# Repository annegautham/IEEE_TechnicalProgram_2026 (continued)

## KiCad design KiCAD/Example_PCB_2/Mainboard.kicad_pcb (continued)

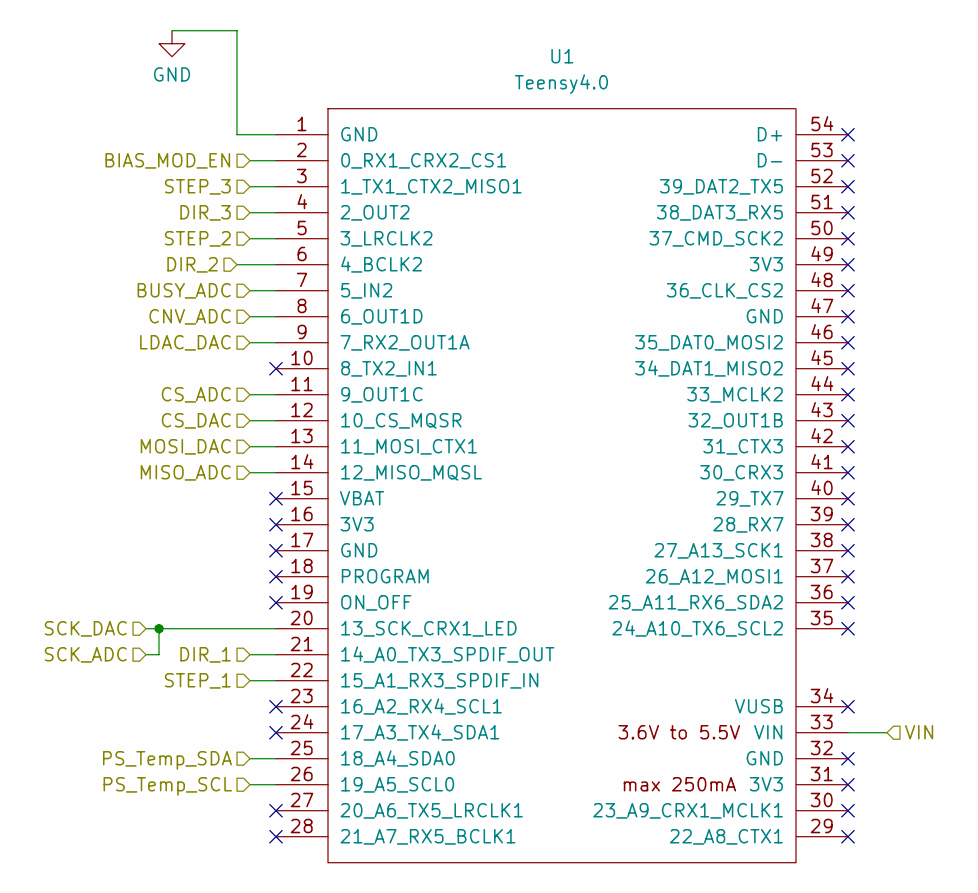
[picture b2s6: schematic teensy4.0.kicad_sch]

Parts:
U1: Teensy4.0; Teensy40

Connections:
+5V: U1.33 (VIN); also elsewhere on the board
/BIAS_MOD_EN: U1.2 (0_RX1_CRX2_CS1); also elsewhere on the board
/BUSY_ADC: U1.7 (5_IN2); also elsewhere on the board
/CNV_ADC: U1.8 (6_OUT1D); also elsewhere on the board
/CS_ADC: U1.11 (9_OUT1C); also elsewhere on the board
/CS_DAC: U1.12 (10_CS_MQSR); also elsewhere on the board
/LDAC_DAC: U1.9 (7_RX2_OUT1A); also elsewhere on the board
/MISO_ADC: U1.14 (12_MISO_MQSL); also elsewhere on the board
/MOSI_DAC: U1.13 (11_MOSI_CTX1); also elsewhere on the board
/PS_Temp_SCL: U1.26 (19_A5_SCL0); also elsewhere on the board
/PS_Temp_SDA: U1.25 (18_A4_SDA0); also elsewhere on the board
/SCK_ADC: U1.20 (13_SCK_CRX1_LED); also elsewhere on the board
/StepperDrivers/DIR_1: U1.21 (14_A0_TX3_SPDIF_OUT); also elsewhere on the board
/StepperDrivers/DIR_2: U1.6 (4_BCLK2); also elsewhere on the board
/StepperDrivers/DIR_3: U1.4 (2_OUT2); also elsewhere on the board
/StepperDrivers/STEP_1: U1.22 (15_A1_RX3_SPDIF_IN); also elsewhere on the board
/StepperDrivers/STEP_2: U1.5 (3_LRCLK2); also elsewhere on the board
/StepperDrivers/STEP_3: U1.3 (1_TX1_CTX2_MISO1); also elsewhere on the board
GND: U1.1 (GND); also elsewhere on the board

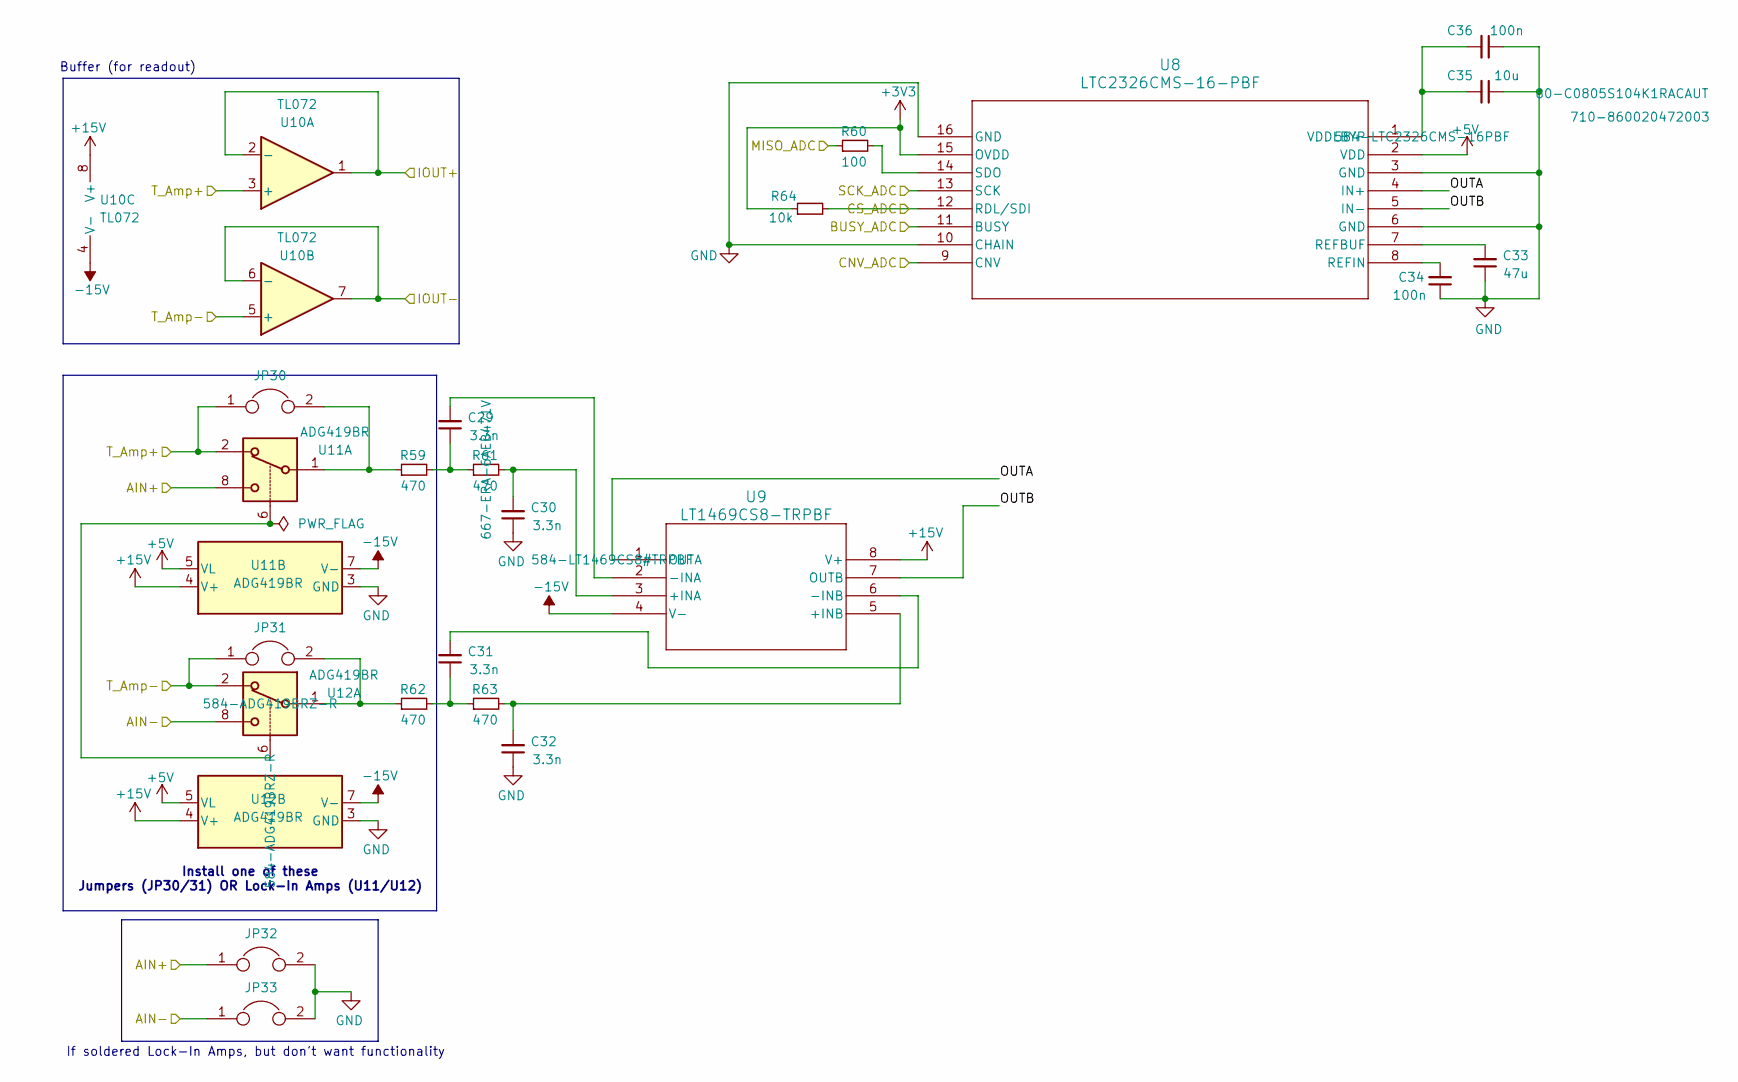
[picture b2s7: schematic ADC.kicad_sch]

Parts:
C29, C30, C31, C32: 3.3n; C_0805_2012Metric; Mouser Part Number 80-C0805C332KCR
C33: 47u; C_0805_2012Metric; Mouser Part Number 80-C0805C476M9P7800
C34, C36: 100n; C_0805_2012Metric; Mouser Part Number 80-C0805S104K1RACAUT
C35: 10u; CP_Radial_D5.0mm_P2.00mm; Mouser Part Number 710-860020472003
JP30, JP31, JP32, JP33: Jumper; SolderJumper-2_P1.3mm_Open_TrianglePad1.0x1.5mm
R59, R61, R62, R63: 470; R_0805_2012Metric; Mouser Part Number 667-ERA-6AEB471V
R60: 100; R_0805_2012Metric; Mouser Part Number 708-RNCA0805BTE100R
R64: 10k; R_0805_2012Metric; Mouser Part Number 755-ESR10EZPD1002
U8: LTC2326CMS-16-PBF; MSOP-16_MS_LIT; Mouser Part Number 584-LTC2326CMS-16PBF
U9: LT1469CS8-TRPBF; SO-8_S_LIT; Mouser Part Number 584-LT1469CS8#TRPBF
U10: TL072; SOIC-8-1EP_3.9x4.9mm_P1.27mm_EP2.29x3mm_ThermalVias; Mouser Part Number 511-TL072BIDT
U11, U12: ADG419BR; SOIC-8_3.9x4.9mm_P1.27mm; Mouser Part Number 584-ADG419BRZ-R

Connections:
+3V3: R64.1, U8.15 (OVDD); also elsewhere on the board
+5V: U8.2 (VDD), U11.5 (VL), U12.5 (VL); also elsewhere on the board
+15V: U9.8 (V+), U10.8 (V+), U11.4 (V+), U12.4 (V+); also elsewhere on the board
-15V: U9.4 (V-), U10.4 (V-), U11.7 (V-), U12.7 (V-); also elsewhere on the board
/ADC/OUTA: U8.4 (IN+), U9.1 (OUTA)
/ADC/OUTB: U8.5 (IN-), U9.7 (OUTB)
/AIN+: JP32.1, U11.8; also elsewhere on the board
/AIN-: JP33.1, U12.8; also elsewhere on the board
/BUSY_ADC: U8.11 (BUSY); also elsewhere on the board
/CNV_ADC: U8.9 (CNV); also elsewhere on the board
/CS_ADC: R64.2, U8.12 (RDL/SDI); also elsewhere on the board
/IOUT+: U10.1, U10.2 (-); also elsewhere on the board
/IOUT-: U10.6 (-), U10.7; also elsewhere on the board
/MISO_ADC: R60.1; also elsewhere on the board
/SCK_ADC: U8.13 (SCK); also elsewhere on the board
/T_Amp+: JP30.1, U10.3 (+), U11.2; also elsewhere on the board
/T_Amp-: JP31.1, U10.5 (+), U12.2; also elsewhere on the board
GND: C30.1, C32.1, C33.1, C34.1, C35.1, C36.1, JP32.2, JP33.2, U8.3 (GND), U8.6 (GND), U8.10 (CHAIN), U8.16 (GND), U11.3 (GND), U12.3 (GND); also elsewhere on the board
unnamed: C29.1, R59.2, R61.1
unnamed: C31.1, R62.2, R63.1
unnamed: JP30.2, R59.1, U11.1
unnamed: JP31.2, R62.1, U12.1
unnamed: C33.2, U8.7 (REFBUF)
unnamed: C34.2, U8.8 (REFIN)
unnamed: R60.2, U8.14 (SDO)
unnamed: C35.2, C36.2, U8.1 (VDDLBYP)
unnamed: C30.2, R61.2, U9.3 (+INA)
unnamed: C32.2, R63.2, U9.5 (+INB)
unnamed: C29.2, U9.2 (-INA)
unnamed: C31.2, U9.6 (-INB)
unnamed: U11.6, U12.6

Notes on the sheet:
Install one of these Jumpers (JP30/31) OR Lock-In Amps (U11/U12)
If soldered Lock-In Amps, but don't want functionality
Buffer (for readout)

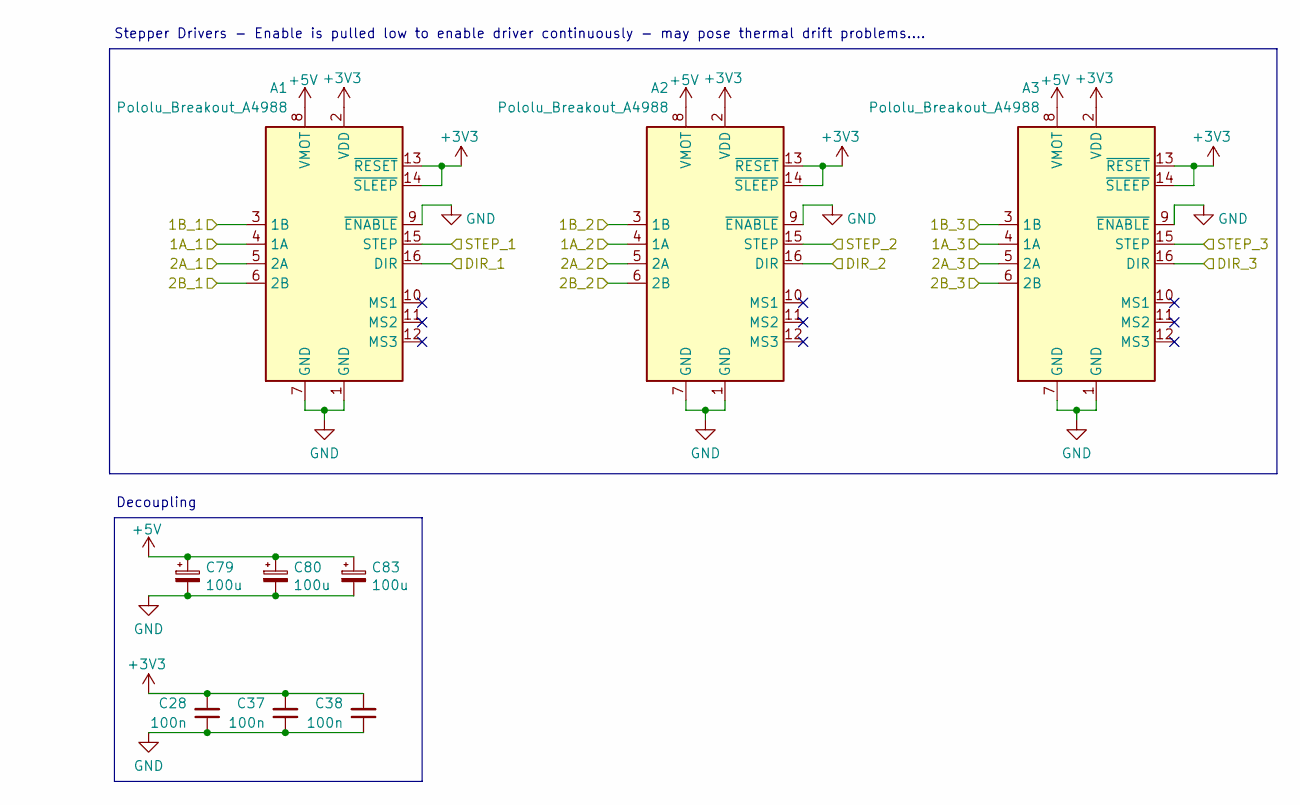
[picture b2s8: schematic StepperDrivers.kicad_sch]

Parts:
A1, A2, A3: Pololu_Breakout_A4988; Pololu_Breakout-16_15.2x20.3mm
C28, C37, C38: 100n; C_0805_2012Metric; Mouser Part Number 80-C0805S104K1RACAUT
C79, C80, C83: 100u; CP_Radial_D6.3mm_P2.50mm; Mouser Part Number 80-ESW107M016AE3EA

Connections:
+3V3: A1.2 (VDD), A1.13 (~RESET), A1.14 (~SLEEP), A2.2 (VDD), A2.13 (~RESET), A2.14 (~SLEEP), A3.2 (VDD), A3.13 (~RESET), A3.14 (~SLEEP), C28.2, C37.2, C38.2; also elsewhere on the board
+5V: A1.8 (VMOT), A2.8 (VMOT), A3.8 (VMOT), C79.1, C80.1, C83.1; also elsewhere on the board
/1A_1: A1.4 (1A); also elsewhere on the board
/1A_2: A2.4 (1A); also elsewhere on the board
/1A_3: A3.4 (1A); also elsewhere on the board
/1B_1: A1.3 (1B); also elsewhere on the board
/1B_2: A2.3 (1B); also elsewhere on the board
/1B_3: A3.3 (1B); also elsewhere on the board
/2A_1: A1.5 (2A); also elsewhere on the board
/2A_2: A2.5 (2A); also elsewhere on the board
/2A_3: A3.5 (2A); also elsewhere on the board
/2B_1: A1.6 (2B); also elsewhere on the board
/2B_2: A2.6 (2B); also elsewhere on the board
/2B_3: A3.6 (2B); also elsewhere on the board
/StepperDrivers/DIR_1: A1.16 (DIR); also elsewhere on the board
/StepperDrivers/DIR_2: A2.16 (DIR); also elsewhere on the board
/StepperDrivers/DIR_3: A3.16 (DIR); also elsewhere on the board
/StepperDrivers/STEP_1: A1.15 (STEP); also elsewhere on the board
/StepperDrivers/STEP_2: A2.15 (STEP); also elsewhere on the board
/StepperDrivers/STEP_3: A3.15 (STEP); also elsewhere on the board
GND: A1.1 (GND), A1.7 (GND), A1.9 (~ENABLE), A2.1 (GND), A2.7 (GND), A2.9 (~ENABLE), A3.1 (GND), A3.7 (GND), A3.9 (~ENABLE), C28.1, C37.1, C38.1, C79.2, C80.2, C83.2; also elsewhere on the board

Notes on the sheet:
Stepper Drivers - Enable is pulled low to enable driver continuously - may pose thermal drift problems....
Decoupling

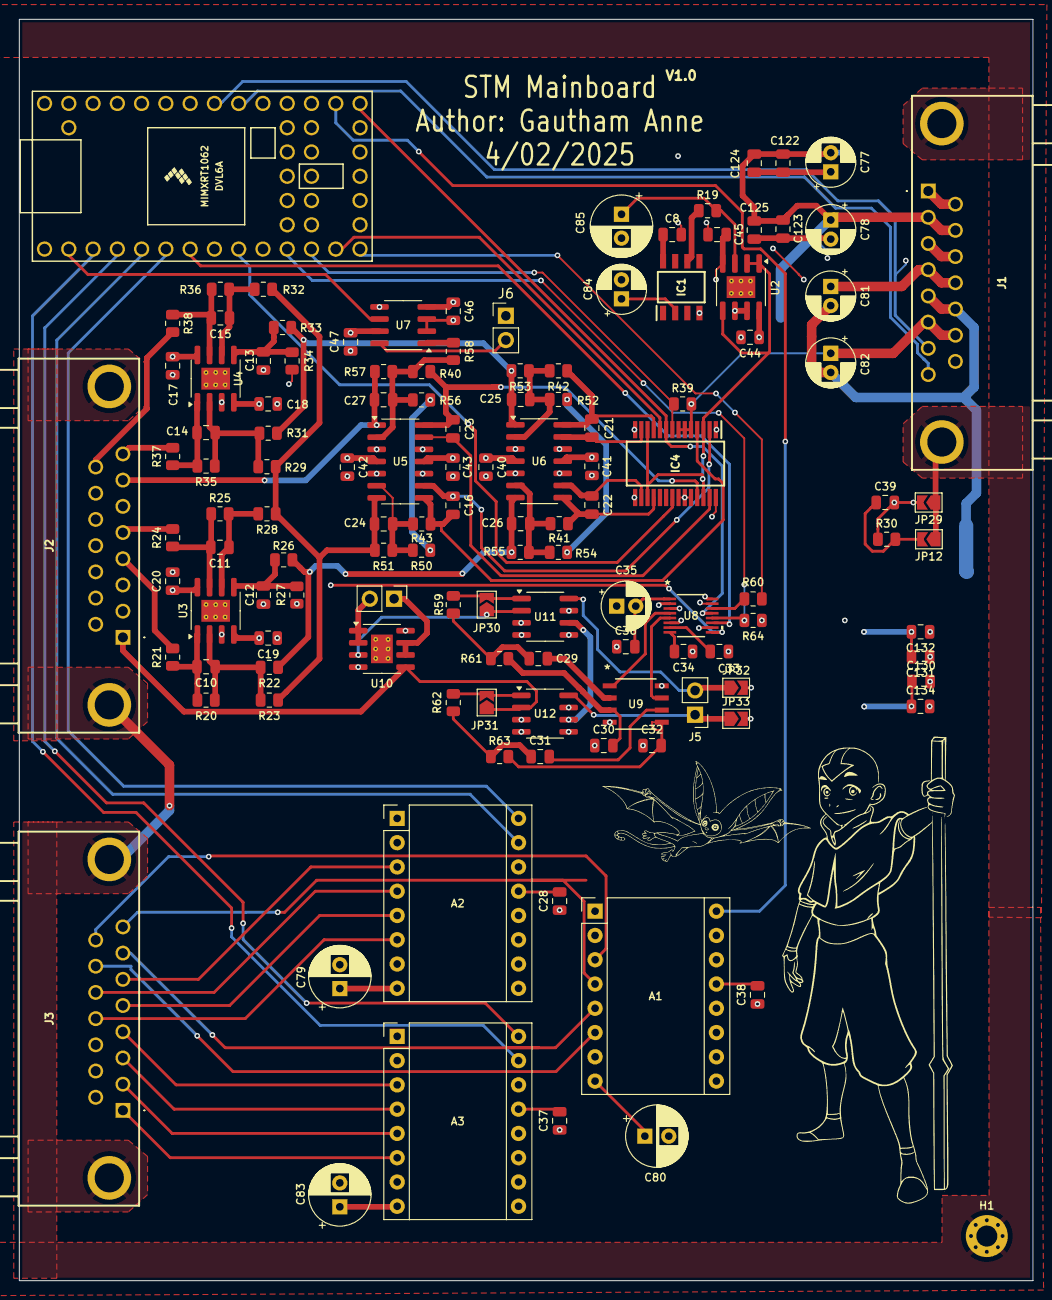
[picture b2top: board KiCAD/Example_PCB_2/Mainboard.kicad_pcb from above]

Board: 4 copper layers, 106.1 x 132.0 mm, 126 parts (0 on the bottom side), 94 nets.

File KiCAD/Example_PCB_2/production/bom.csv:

Designator,Footprint,Quantity,Value,LCSC Part #
"A1, A2, A3",Pololu_Breakout-16_15.2x20.3mm,3,Pololu_Breakout_A4988,
"C10, C11, C12, C13, C14, C15, C24, C25, C26, C27",0805,10,4.7n,
"C122, C123, C124, C125, C130, C131, C132, C134",0805,8,100n,
"C16, C21, C22, C23, C29, C30, C31, C32",0805,8,3.3n,
"C17, C18, C19, C20, C39, C40, C41, C42, C43, C44, C45, C46, C47",0805,13,100n,C14663
"C28, C34, C36, C37, C38",0805,5,100n,
C33,0805,1,47u,
"C35, C77, C78, C81, C82, C84",CP_Radial_D5.0mm_P2.00mm,6,10u,
"C79, C80, C83, C85",CP_Radial_D6.3mm_P2.50mm,4,100u,
C8,0805,1,2.2u,
IC1,SOIC127P600X175-8N,1,REF102AU_2K5,
IC4,SOP65P780X200-28N,1,DAC8814IBDBT,
"J1, J2, J3",57457826,3,5745782-6,
"J4, J5, J6",PinHeader_1x02_P2.54mm_Vertical,3,Conn_01x02_Pin,
"JP12, JP29, JP30, JP31, JP32, JP33",SolderJumper-2_P1.3mm_Open_TrianglePad1.0x1.5mm,6,Jumper,
R19,0805,1,1k,
"R20, R22, R23, R25, R26, R27, R28, R29, R31, R32, R33, R34, R35, R36, R50, R51, R52, R53, R54, R55, R56, R57, R58",0805,23,3k,
"R21, R24, R37, R38",0805,4,220,
R30,0805,1,1M2,C22107
"R39, R64",0805,2,10k,
"R40, R41, R42, R43",0805,4,1.5k,
"R59, R61, R62, R63",0805,4,470,
R60,0805,1,100,
U1,Teensy40,1,Teensy4.0,
"U10, U2, U3, U4",SOIC-8-1EP_3.9x4.9mm_P1.27mm_EP2.29x3mm_ThermalVias,4,TL072,
"U11, U12, U7",SOIC-8_3.9x4.9mm_P1.27mm,3,ADG419BR,
"U5, U6",SOIC-14_3.9x8.7mm_P1.27mm,2,TL074,
U8,MSOP-16_MS_LIT,1,LTC2326CMS-16-PBF,
U9,SO-8_S_LIT,1,LT1469CS8-TRPBF,

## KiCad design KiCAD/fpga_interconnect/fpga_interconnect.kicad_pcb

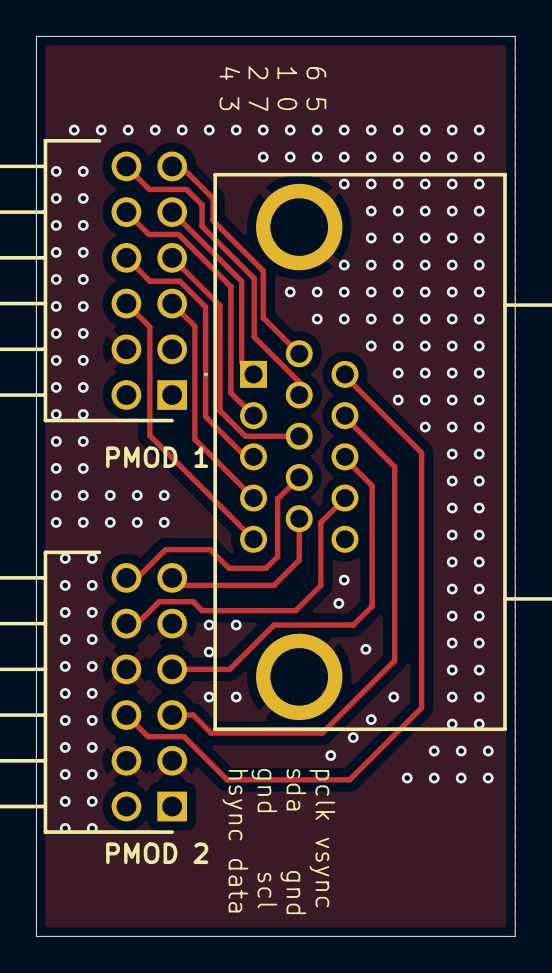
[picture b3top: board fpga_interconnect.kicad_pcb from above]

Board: 2 copper layers, 26.6 x 50.0 mm, 3 parts (0 on the bottom side), 15 nets.

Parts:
J1: VGA; AHDF15AKGTAXB
J2: Pmod 1; HDRRA12W63P254_2X6_1514X280X635P
J3: Pmod 2; HDRRA12W63P254_2X6_1514X280X635P

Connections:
/DATAEN_CMD: J1.12, J3.5
/HSYNC: J1.11, J3.6
/IIC1_SCL: J1.13, J3.7
/IIC1_SDA: J1.14, J3.10
/PCLK: J1.9, J3.12
/PDATA0: J1.1, J2.9
/PDATA1: J1.2, J2.10
/PDATA2: J1.3, J2.8
/PDATA3: J1.4, J2.5
/PDATA4: J1.5, J2.6
/PDATA5: J1.6, J2.11
/PDATA6: J1.7, J2.12
/PDATA7: J1.8, J2.7
/VSYNC: J1.10, J3.11
GND: J1.15, J1.MH1, J1.MH2, J2.3, J2.4, J3.3, J3.4, J3.8, J3.9

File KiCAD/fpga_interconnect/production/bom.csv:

Designator,Footprint,Quantity,Value,LCSC Part #
J1,AHDF15AKGTAXB,1,VGA,
J2,HDRRA12W63P254_2X6_1514X280X635P,1,Pmod 1,
J3,HDRRA12W63P254_2X6_1514X280X635P,1,Pmod 2,

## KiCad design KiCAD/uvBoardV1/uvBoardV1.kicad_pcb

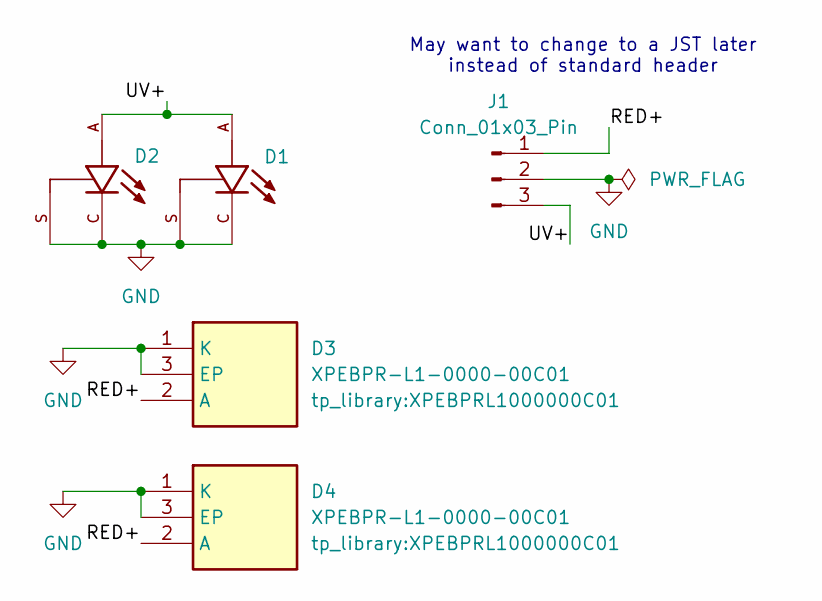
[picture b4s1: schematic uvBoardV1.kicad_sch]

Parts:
D1, D2: SST-10-UV-A130-G405-00; LED_SST-10-UV-A130-G405-00; PARTREV 05
D3, D4: XPEBPR-L1-0000-00C01; XPEBPRL1000000C01; Mouser Part Number 941-XPEBPRL10000C01
J1: Conn_01x03_Pin; PinHeader_1x03_P2.54mm_Vertical

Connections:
/RED+: D3.2 (A), D4.2 (A), J1.1
/UV+: D1.A, D2.A, J1.3
GND: D1.C, D1.S, D2.C, D2.S, D3.1 (K), D3.3 (EP), D4.1 (K), D4.3 (EP), J1.2

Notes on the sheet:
May want to change to a JST later instead of standard header

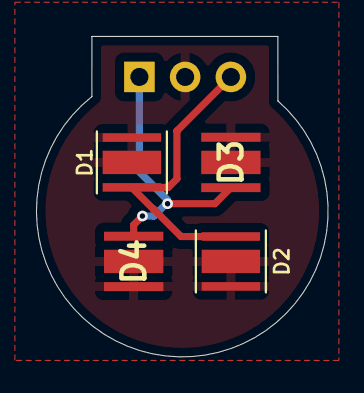
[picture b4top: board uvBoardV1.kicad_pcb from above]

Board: 2 copper layers, 16.2 x 17.8 mm, 5 parts (1 on the bottom side), 3 nets.

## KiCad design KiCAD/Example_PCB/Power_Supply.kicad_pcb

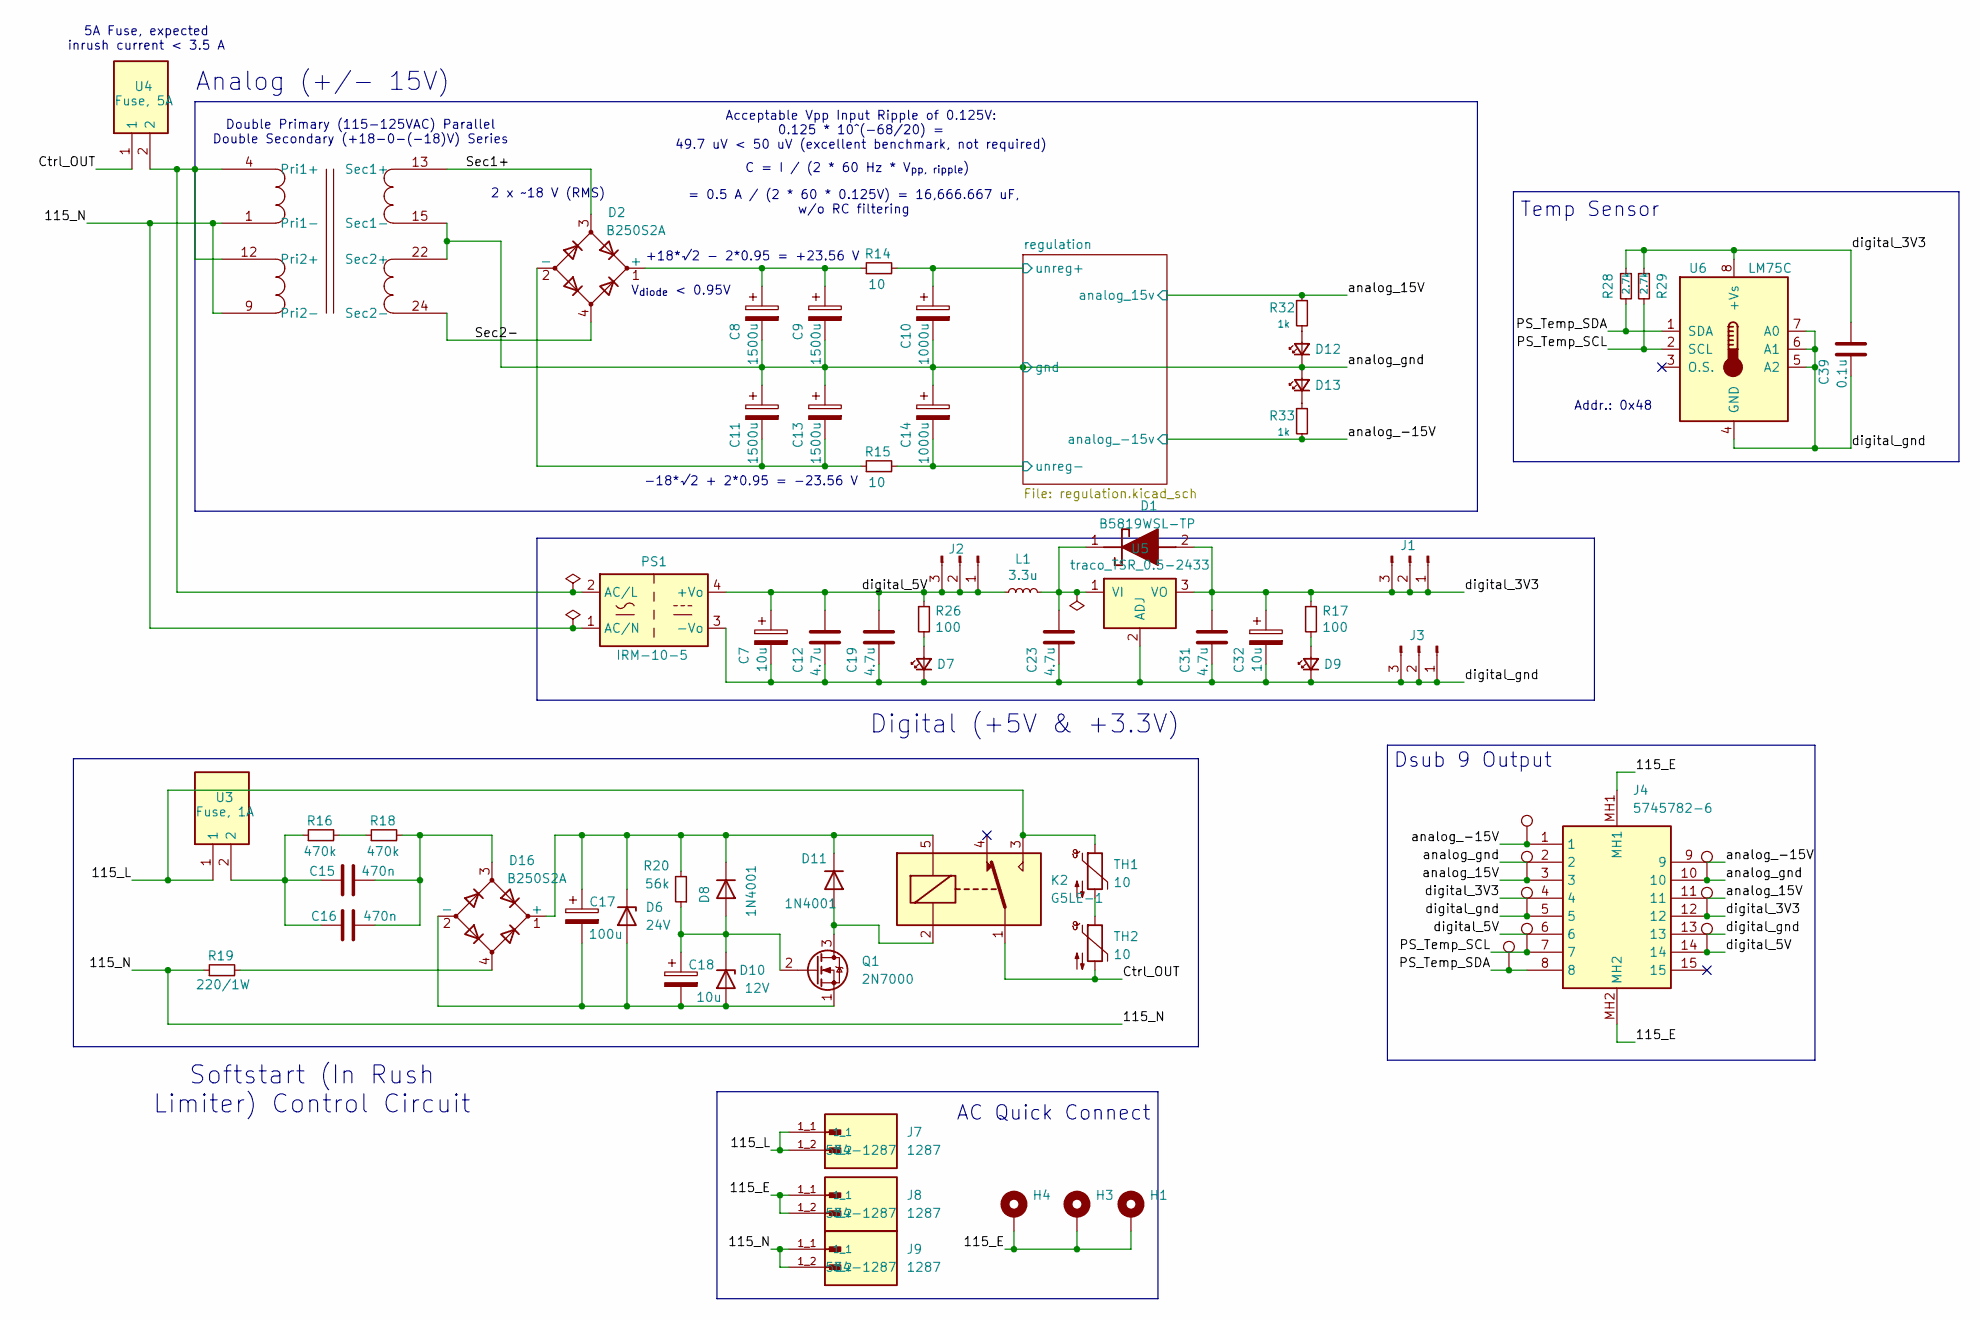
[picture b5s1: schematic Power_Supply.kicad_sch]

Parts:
C7, C32: 10u; CP_EIA-7343-31_Kemet-D; Mouser Part Number 80-T491D106K025
C8, C9, C11, C13: 1500u; CP_Radial_D12.5mm_P5.00mm_+Better; Mouser Part Number 647-UHW1H152MHD
C10, C14: 1000u; CP_Radial_D12.5mm_P5.00mm_+Better; Mouser Part Number 647-UHW1H102MHD
C12, C19, C23, C31: 4.7u; C_0603_1608Metric; Mouser Part Number 187-CL10A475KO8NQNC
C15, C16: 470n; CAP_R46KN347000N0M_KEM; Mouser Part Number 80-R46KN347000N0M
C17: 100u; C_Radial_D10.0mm_H12.5mm_P5.00mm; Mouser Part Number 594-2222-140-50101
C18: 10u; CP_Radial_D5.0mm_P2.00mm; Mouser Part Number 710-860010372001
C39: 0.1u; C_0603_1608Metric; Mouser Part Number 80-C0603C104J1RAUTO7
D1: B5819WSL-TP; SODFL2512X90N; Mouser Part Number 833-B5819WSL-TP
D2, D16: B250S2A; P20_SO-DIL-Slim; Mouser Part Number 637-B250S2A-SLIM
D6: 24V; D_SOD-123; Mouser Part Number 863-SZMMSZ4709T1G
D7, D9, D12, D13: LED_Small; LED_0603_1608Metric
D8, D11: 1N4001; D_DO-41_SOD81_P10.16mm_Horizontal; Mouser Part Number 637-1N4001
D10: 12V; D_SOD-123; Mouser Part Number 78-MMSZ4699-HE3_A-08
H1, H3, H4: MountingHole_Pad; MountingHole_3.2mm_M3_Pad_Via
J1, J2, J3: Conn_01x03_Pin; PinHeader_1x03_P2.54mm_Vertical
J4: 5745782-6; 57457826; Mouser Part Number 571-5745782-6
J7, J8, J9: 1287; KEYSTONE_1287; PARTREV F; Mouser Part Number 534-1287
K2: G5LE-1; Relay_SPDT_Omron-G5LE-1; Mouser Part Number 653-G5LE-1-SDC24
L1: 3.3u; IND_BOURNS_SRR1280; Mouser Part Number 652-SRR1280-3R3Y
PS1: IRM-10-5; Converter_ACDC_MeanWell_IRM-10-xx_THT; Mouser Part Number 709-IRM10-5
Q1: 2N7000; TO-92_Inline; Mouser Part Number 512-2N7000
R14, R15: 10; R_1206_3216Metric; Mouser Part Number 71-RCC120610R0JNEA
R16, R18: 470k; R_Axial_DIN0207_L6.3mm_D2.5mm_P15.24mm_Horizontal; Mouser Part Number 71-CCF07470KJKE36
R17, R26: 100; R_0805_2012Metric; Mouser Part Number 710-560112120020
R19: 220/1W; R_2512_6332Metric; Mouser Part Number 279-3520220RJT
R20: 56k; R_0805_2012Metric; Mouser Part Number 755-ESR10EZPF5602
R28, R29: 2.7k; R_0805_2012Metric; Mouser Part Number 603-AA0805JR-072K7L
R32, R33: 1k; R_0805_2012Metric
T1: FLN_40_18
TH1, TH2: 10; R_Axial_DIN0204_L3.6mm_D1.6mm_P5.08mm_Horizontal; Mouser Part Number 995-SL10-10002
TP1, TP2, TP3, TP4, TP5, TP6, TP7, TP8: TestPoint; TestPoint_Loop_D1.80mm_Drill1.0mm_Beaded; Mouser Part Number 534-5005
U3: Fuse, 1A; 0PTF0078P; Mouser Part Number 576-0PTF0078P
U4: Fuse, 5A; 0PTF0078P; Mouser Part Number 576-0PTF0078P
U5: traco_TSR_0.5-2433; TSR-0.5-2433; Mouser Part Number 495-TSR0.5-2433
U6: LM75C; SOIC-8_3.9x4.9mm_P1.27mm; Mouser Part Number 700-LM75BIM-3+

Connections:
/115_E: H1.1, H3.1, H4.1, J4.MH1, J4.MH2, J8.1_1, J8.1_2
/115_L: J7.1_1, J7.1_2, K2.3, TH1.1, U3.1
/115_N: J9.1_1, J9.1_2, PS1.1 (AC/N), R19.1, T1.1 (Pri1-), T1.9 (Pri2-)
/Ctrl_OUT: K2.1, TH2.2, U4.1
/PS_Temp_SCL: J4.7, R29.2, TP7.1, U6.2 (SCL)
/PS_Temp_SDA: J4.8, R28.2, TP8.1, U6.1 (SDA)
/Sec1+: D2.3, T1.13 (Sec1+)
/Sec2-: D2.4, T1.24 (Sec2-)
/analog_15V: J4.3, J4.11, R32.1, TP3.1; also elsewhere on the board
/analog_-15V: J4.1, J4.9, R33.2, TP1.1; also elsewhere on the board
/analog_gnd: C8.2, C9.2, C10.2, C11.1, C13.1, C14.1, D12.1 (K), D13.2 (A), J4.2, J4.10, T1.15 (Sec1-), T1.22 (Sec2+), TP2.1; also elsewhere on the board
/digital_3V3: C31.1, C32.1, C39.1, D1.2 (A), J1.1, J1.2, J1.3, J4.4, J4.12, R17.1, R28.1, R29.1, TP4.1, U5.3 (VO), U6.8 (+Vs)
/digital_5V: C7.1, C12.1, C19.1, J2.1, J2.2, J2.3, J4.6, J4.14, L1.1, PS1.4 (+Vo), R26.1, TP6.1
/digital_gnd: C7.2, C12.2, C19.2, C23.2, C31.2, C32.2, C39.2, D7.1 (K), D9.1 (K), J3.1, J3.2, J3.3, J4.5, J4.13, PS1.3 (-Vo), TP5.1, U5.2 (ADJ), U6.4 (GND), U6.5 (A2), U6.6 (A1), U6.7 (A0)
/regulation/unreg+: C10.1, R14.2; also elsewhere on the board
/regulation/unreg-: C14.2, R15.2; also elsewhere on the board
unnamed: C15.1, C16.1, R16.1, U3.2
unnamed: C15.2, C16.2, D16.3, R18.2
unnamed: C23.1, D1.1 (K), L1.2, U5.1 (VI)
unnamed: C8.1, C9.1, D2.1 (+), R14.1
unnamed: C11.2, C13.2, D2.2 (-), R15.1
unnamed: D7.2 (A), R26.2
unnamed: D9.2 (A), R17.2
unnamed: C17.2, C18.2, D6.2 (A), D10.2 (A), D16.2 (-), Q1.1 (S)
unnamed: C18.1, D8.2 (A), D10.1 (K), Q1.2 (G), R20.1
unnamed: D11.2 (A), K2.2, Q1.3 (D)
unnamed: C17.1, D6.1 (K), D8.1 (K), D11.1 (K), D16.1 (+), K2.5, R20.2
unnamed: D12.2 (A), R32.2
unnamed: D13.1 (K), R33.1
unnamed: D16.4, R19.2
unnamed: PS1.2 (AC/L), T1.4 (Pri1+), T1.12 (Pri2+), U4.2
unnamed: R16.2, R18.1
unnamed: TH1.2, TH2.1

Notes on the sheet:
Dsub 9 Output
Addr.: 0x48
Analog (+/- 15V)
5A Fuse, expected inrush current < 3.5 A
Acceptable Vpp Input Ripple of 0.125V: 0.125 * 10^(-68/20) = 49.7 uV < 50 uV (excellent benchmark, not required)
Double Primary (115-125VAC) Parallel Double Secondary (+18-0-(-18)V) Series
Softstart (In Rush Limiter) Control Circuit
-18*√2 + 2*0.95 = -23.56 V
C = I / (2 * 60 Hz * V_{pp, ripple})
V_{diode} < 0.95V
AC Quick Connect
2 x ~18 V (RMS)
Temp Sensor
+18*√2 - 2*0.95 = +23.56 V
Digital (+5V & +3.3V)
= 0.5 A / (2 * 60 * 0.125V) = 16,666.667 uF, w/o RC filtering

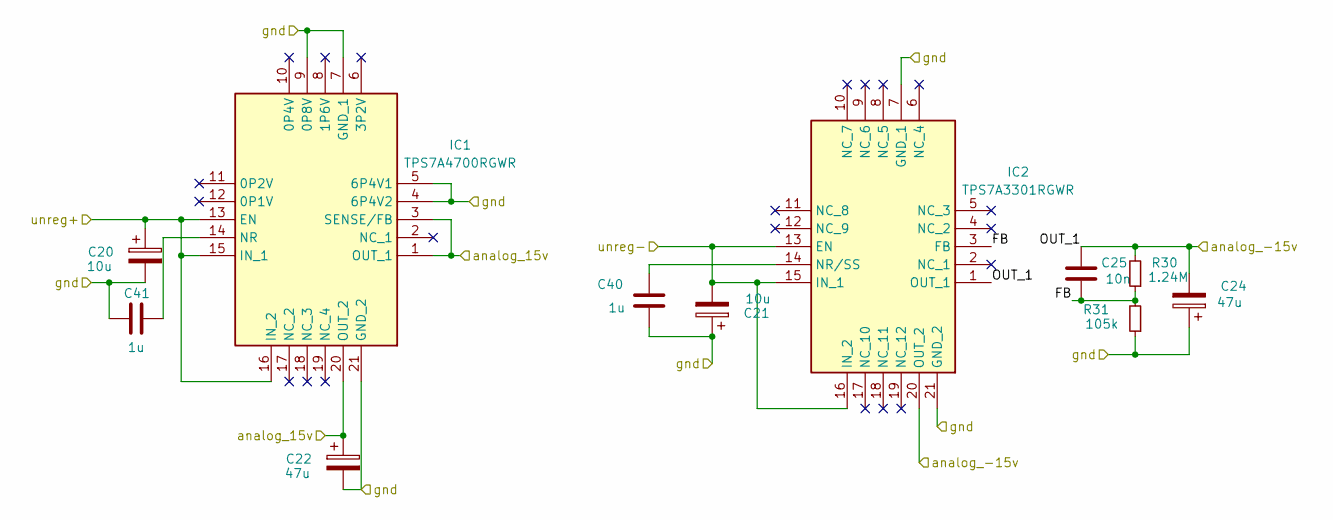
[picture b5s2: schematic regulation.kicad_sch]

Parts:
C20, C21: 10u; CP_EIA-7343-31_Kemet-D; Mouser Part Number 80-T491D106K025
C22, C24: 47u; CP_EIA-7343-31_Kemet-D; Mouser Part Number 80-T491D476K020
C25: 10n; C_0603_1608Metric; Mouser Part Number 581-06033C103KAZ2A
C40, C41: 1u; C_0603_1608Metric; Mouser Part Number 963-MLASU168SB5105KT
IC1: TPS7A4700RGWR; QFN65P500X500X100-21N-D; Mouser Part Number 595-TPS7A4700RGWR
IC2: TPS7A3301RGWR; QFN65P500X500X100-21N-D; Mouser Part Number 595-TPS7A3301RGWR
R30: 1.24M; R_0805_2012Metric; Mouser Part Number 71-CRCW08051M24FKEA
R31: 105k; R_0805_2012Metric; Mouser Part Number 279-RQ73C2A105KBTD

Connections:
/analog_15V: C22.1, IC1.1 (OUT_1), IC1.3 (SENSE/FB), IC1.20 (OUT_2); also elsewhere on the board
/analog_-15V: C24.2, C25.1, IC2.1 (OUT_1), IC2.20 (OUT_2), R30.2; also elsewhere on the board
/analog_gnd: C20.2, C21.1, C22.2, C24.1, C40.2, C41.2, IC1.4 (6P4V2), IC1.5 (6P4V1), IC1.7 (GND_1), IC1.9 (0P8V), IC1.21 (GND_2), IC2.7 (GND_1), IC2.21 (GND_2), R31.1; also elsewhere on the board
/regulation/FB: C25.2, IC2.3 (FB), R30.1, R31.2
/regulation/unreg+: C20.1, IC1.13 (EN), IC1.15 (IN_1), IC1.16 (IN_2); also elsewhere on the board
/regulation/unreg-: C21.2, IC2.13 (EN), IC2.15 (IN_1), IC2.16 (IN_2); also elsewhere on the board
unnamed: C41.1, IC1.14 (NR)
unnamed: C40.1, IC2.14 (NR/SS)

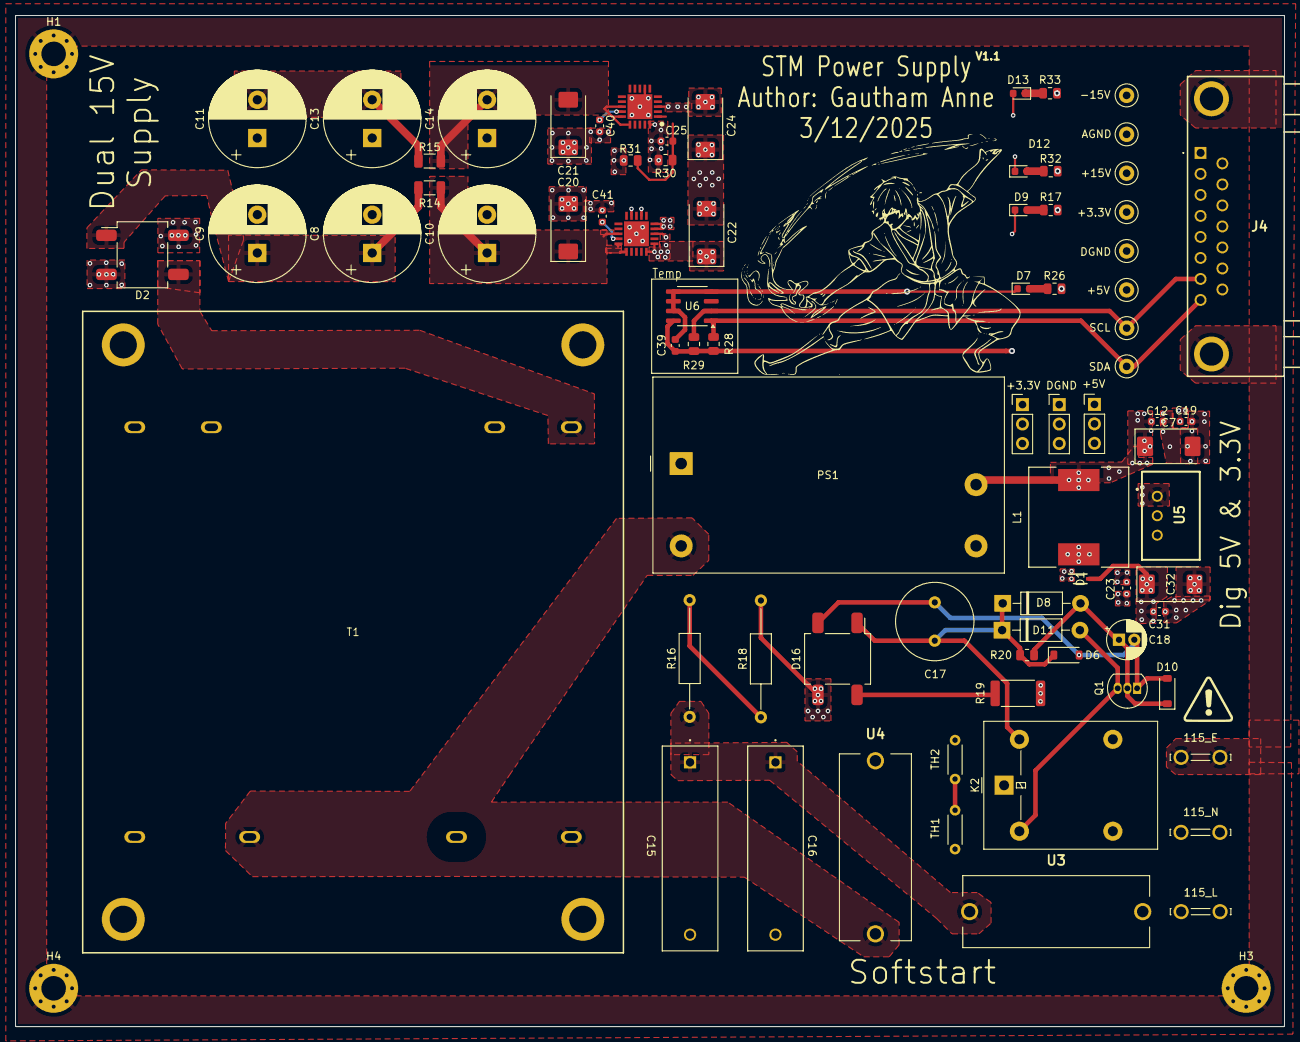
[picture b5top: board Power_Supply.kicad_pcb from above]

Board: 4 copper layers, 165.7 x 132.0 mm, 80 parts (0 on the bottom side), 36 nets.

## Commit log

2026-01-31 example pcb + diffraction eff calculator
2026-02-02 empty pcb and sch files
2026-02-02 added a non-functioning .py file that's supposed to generate the footprint, needs debugging and entering correct values cause this is ai's work
2026-02-06 library .pretty is created, with DLPC footprint python code successfully generting footprint, should double check if the specefications match datasheet exactly
2026-02-06 added four boards in a root screen sheet
2026-02-12 crime
2026-02-14 uv pcb
2026-02-14 bga footprint addition
2026-02-15 symbol add
2026-02-15 dlpa2005 symbol + footprint added to proj specific library
2026-02-15 some doofus goofus
2026-02-15 Val's edit
2026-02-15 val new edit brr
2026-02-16 changed tp_library to read & write
2026-02-16 stepper updates
2026-02-16 moved capacitor
2026-02-17 pain! dmd interface grind part 1
2026-02-17 spi connections to dlpc
2026-02-17 dmd interface done!
2026-02-18 humanly readable now
2026-02-18 more readable
2026-02-18 some new schematics
2026-02-18 some schematic layout power
2026-02-18 WIP dmd interface; made assembly for DMD, started new board for DMD interconnect
2026-02-18 assembly for lga footprint
2026-02-19 almost done with VSS, VDD without power souce schematics
2026-02-20 no major changes
2026-02-21 fixed some DRC error
2026-02-21 didn't really change mainboard
2026-02-23 non finished changes
2026-02-24 commiting progress hope this doesn't crash
2026-02-24 DLPC pins all connected to pin, some circutry incomplete inclding LEDs, SPI, Crystal Ocillator, and DLPC programming flash. I also need to import a symbol and footprint for the ferrite beads, and som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
2026-02-24 relative library paths
2026-02-25 firmware for stepper
2026-02-25 software gui update
2026-02-26 pully pull
2026-02-26 #stillonthegrind
2026-02-26 yaaaa
2026-02-26 minor changed
2026-02-27 Changed all FPGA Connections to what we want, created a new project for the connection board
2026-02-28 actually saved the file this time
2026-02-28 SPI and prog connection
2026-02-28 Added our connector board from FPGA to main board
2026-02-28 added 3d models to FPGA Board
2026-02-28 fixed bus connection on fpga connector
2026-03-01 fixed pdata bus connection
2026-03-01 fixed funny bus connectinos
2026-03-01 gpios are now hierarchicals
2026-03-01 fixed spi1 dlpc connections
2026-03-01 fixed all proj specific compoents
2026-03-01 name changes cuz i like lowercase
2026-03-01 fun changes
2026-03-01 uv board productino files
2026-03-01 dmd interconnect work 1st pass
2026-03-01 mainboard pain
2026-03-01 Complete FPGA interconnect
2026-03-01 DLPC schematic looks a bit prettier now, ERC needs to be resolved, the vast majority of errors are because global label is not connected to anything, a good amount of housekeeping left before I can s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
2026-03-03 productino files
2026-03-03 added interactive html bom for fpga interconnect
2026-03-04 first pass optics
2026-03-05 Backlink to CADLAB.io has been added.
2026-03-05 added footprints
2026-03-05 designator names fixed
2026-03-05 rawr
2026-03-06 Testing Motors code added
2026-03-07 fixed VSS, VDD, VCC labels to match their hierarchical counterparts
2026-03-07 added text labels with explainations, check out the updates spreadsheet too - still not complete
2026-03-08 designator names on global finally
2026-03-08 fixed more ERCs
2026-03-09 started power gen input schematic, need to source correct input for 5V buck converter, finished 5V to 3v3 buck converter, need to start the 1.2, 1.8, and buffer 3v3
2026-03-09 don't recall, some ERC prob
2026-03-13 production file updates
2026-03-13 removed question marks
2026-03-13 retry val schematic
2026-03-15 no more question marks!
2026-03-24 added libraries and symbols and step for ferrite beads and D7 LED
2026-03-25 added sym mod and step for resistors but package 0805
2026-03-25 replaced with 0805 all passives in DLPC
2026-03-26 capacitors placed back in place
2026-03-28 changes to all schematic files fixing ERC errors
2026-03-29 more ERC knocked out
2026-03-29 layout, was able to fanout all not power signals without vias inside BGA, will only need normal vias size 0.3mm diameter for GND and power planes, plan is to have DMD signals on their own layer
2026-03-29 added pours to pcb and fixed DLPC capacitor errors
2026-03-29 meeting edits to DLPA and DLPC
2026-03-31 fpga pipline
2026-03-31 added more CRC stuff for both PC teensy and teensy FPGA
2026-03-31 made actual mask that fits what we need
2026-03-31 got rid of the big resolution testing GDS file since its too big or smth
2026-04-01 better litho mask, macro, and created an image stitcher
2026-04-01 added netclasses and added signals to BGA_Signal, still have to add rest of of signals to other classes but now I'm confused on how BGA traces are smaller but then the same signal could use thicker t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
2026-04-01 BGA layout cont
2026-04-02 decoupling caps and pullup down resistors layout
2026-04-03 added border markers and crosshair (center) to lithomask, tested all files here and they all work
2026-04-03 im actually the goat
2026-04-03 i hope this doesn't mess things
2026-04-03 another push schemtic changes
2026-04-04 pcb update, some vias are violating DRC
2026-04-04 added cleanImages to remove black squares on the star, adjusted imagestitcher and imagetoteensy to use that function, updated macro for better resolution
2026-04-05 nothing to report
2026-04-05 more layout stuff
2026-04-05 layout
2026-04-06 i hope no layout changes have been made before this pull
2026-04-07 more layout
2026-04-07 werid GPIO, PDATA, and JTAG routes that prob need redoing
2026-04-08 layout GPIO connector and TSTP
2026-04-10 getting started on power generation
2026-04-15 changed back to sending one image at a time for testing
2026-04-16 made everything on computer side cleaner and modular
2026-04-17 work
2026-04-18 Added FPGA files
2026-04-18 updated footprint to new IEEE folder
2026-04-20 added comments, cleaned up files, added documentation
2026-04-20 added documentation for teensy code
2026-04-20 all documentation for computer and teensy as well as code is fully written, off to FPGA modules now yippee
2026-04-20 fixed bugs in main.cpp teensy
2026-04-20 fully tested code without FPGA, works
2026-04-22 Remove remaining .DS_Store files from tracking
2026-04-22 refactor
2026-04-24 some extra work
2026-04-26 add open loop manipulator firmware and gui
    Drop the firmware (MotionControllerRP) and gui folders from the
    MicroManipulatorStepper open-loop fork into a new openloopfirmware/
    directory so the IEEE technical program repo has a copy of the
    working stepper-driver code.
2026-04-26 move openloopfirmware under KiCAD/stepper/firmware and add README
    Relocate the firmware/gui drop into the existing
    KiCAD/stepper/firmware tree so it sits alongside the upstream
    MotionControllerRP reference and TestingMotors. Add a README
    covering hardware pinout, coil-pair identification, build/flash
    steps, the GUI, the M17/M18/M50/M60/M204/G0 protocol, and the
    common wiring/driver failure modes.
2026-04-26 clean up requirements, harden transform.json load, document single-motor caveat
    - requirements.txt: dedup numpy/pyserial/numpy-quaternion; comment out
    opencv-python and pypylon (only needed when a camera is wired up).
    Default headless config now installs cleanly with pip.
    - mainwindow.py: load_transform now checks for transform.json existence
    and shows a friendly warning instead of an unhandled FileNotFoundError;
    switch raw open() calls to with-statements so files close on errors.
2026-04-26 added reference board inside the pcb and successfully integrated the DLPA chip with its nets
2026-04-30 schematic chagnesS
2026-05-02 make a new copy of the board hopefull yit's an actual seperate copy, tried to change footprintps to match BOM, dismanteled most of the old work, looks promising
2026-05-02 idk man maybe didn't save before last commit
2026-05-02 schematic changes
2026-05-05 idk what's getting committed
2026-05-09 changes to pick and place TI design
2026-05-09 schematic changes - zero DRC errors but I have things to dicuss, and layout footprint work and rearrangment
2026-05-11 DLPA layout
